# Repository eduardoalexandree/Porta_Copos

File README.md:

# Porta_Copos
TCC Engenharia Eletrônica, Eduardo Alexandre

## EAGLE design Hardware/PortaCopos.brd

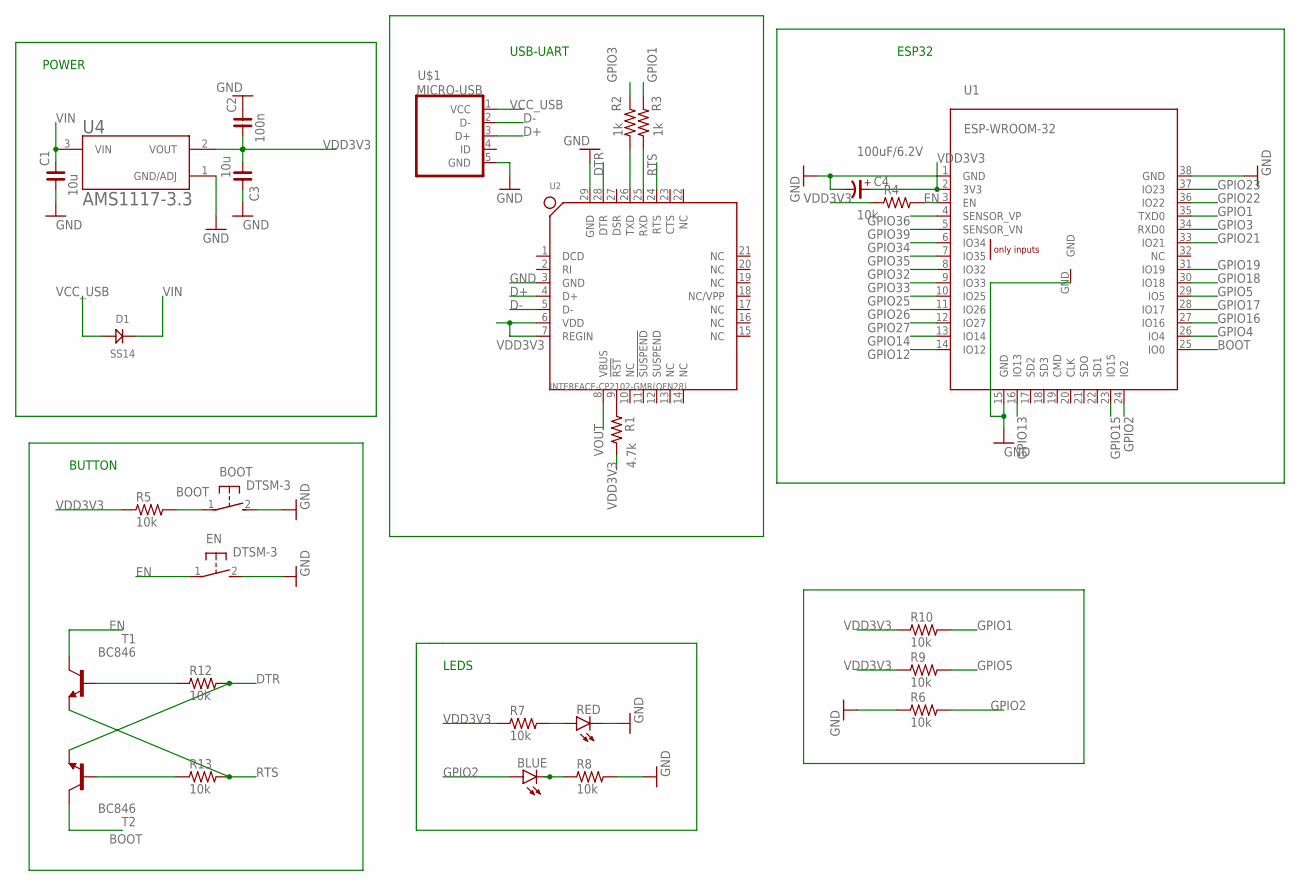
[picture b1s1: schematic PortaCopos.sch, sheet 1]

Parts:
BLUE: blue; CHIPLED_0603
BOOT: DTSM-3
C1, C3: 10u; C0603
C2: 100n; C0603
C4: 100uF/6.2V; C3216-18/T
D1: SS14; DO214
EN: DTSM-3
R1: 4.7k; R0603
R2, R3: 1k; R0603
R4, R5, R6, R7, R8, R9, R10, R12, R13: 10k; R0603
RED: red; CHIPLED_0603
T1, T2: BC846; SOT23
U1: ESP-WROOM-32
U2: INTERFACE-CP2102-GMR(QFN28); QFN28G_0.5-5X5MM
U4: AMS1117-3.3; SOT229P700X180-4N
U$1: MICRO-USB; MICRO-USB-2

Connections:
BOOT: BOOT.1, R5.2, T2.3 (C), U1.25 (IO0)
D+: U2.4 (D+), U$1.3 (D+)
D-: U2.5 (D-), U$1.2 (D-)
DTR: R12.2, T2.2 (E), U2.28 (DTR)
EN: EN.1, R4.2, T1.3 (C), U1.3 (EN)
GND: BOOT.2, C1.1, C2.2, C3.2, C4.-, EN.2, R6.1, R8.2, RED.C, U1.1 (GND), U1.15 (GND), U1.38 (GND), U1.GND, U2.3 (GND), U2.29 (GND), U4.1 (GND/ADJ), U$1.5 (GND); also elsewhere on the board
GPIO1: R3.1, R10.2, U1.35 (TXD0)
GPIO2: BLUE.A, R6.2, U1.24 (IO2)
GPIO3: R2.1, U1.34 (RXD0)
GPIO4: U1.26 (IO4); also elsewhere on the board
GPIO5: R9.2, U1.29 (IO5)
GPIO12: U1.14 (IO12)
GPIO13: U1.16 (IO13)
GPIO14: U1.13 (IO14)
GPIO15: U1.23 (IO15)
GPIO16: U1.27 (IO16); also elsewhere on the board
GPIO17: U1.28 (IO17)
GPIO18: U1.30 (IO18)
GPIO19: U1.31 (IO19)
GPIO21: U1.33 (IO21)
GPIO22: U1.36 (IO22)
GPIO23: U1.37 (IO23)
GPIO25: U1.10 (IO25)
GPIO26: U1.11 (IO26)
GPIO27: U1.12 (IO27)
GPIO32: U1.8 (IO32)
GPIO33: U1.9 (IO33)
GPIO34: U1.6 (IO34)
GPIO35: U1.7 (IO35)
GPIO36: U1.4 (SENSOR_VP)
GPIO39: U1.5 (SENSOR_VN)
unnamed: R1.1, U2.9 (!RST)
unnamed: R2.2, U2.26 (TXD)
unnamed: R3.2, U2.25 (RXD)
unnamed: R12.1, T1.1 (B)
unnamed: R13.1, T2.1 (B)
unnamed: BLUE.C, R8.1
unnamed: R7.2, RED.A
RTS: R13.2, T1.2 (E), U2.24 (RTS)
VCC_USB: D1.ANODE, U$1.1 (VCC)
VDD3V3: C2.1, C3.1, C4.+, R1.2, R4.1, R5.1, R7.1, R9.1, R10.1, U1.2 (3V3), U2.6 (VDD), U2.7 (REGIN), U4.2 (VOUT); also elsewhere on the board
VIN: C1.2, D1.CATHODE (KATHODE), U4.3 (VIN)
VOUT: U2.8 (VBUS)

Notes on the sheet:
POWER
ESP32
USB-UART
BUTTON
LEDS

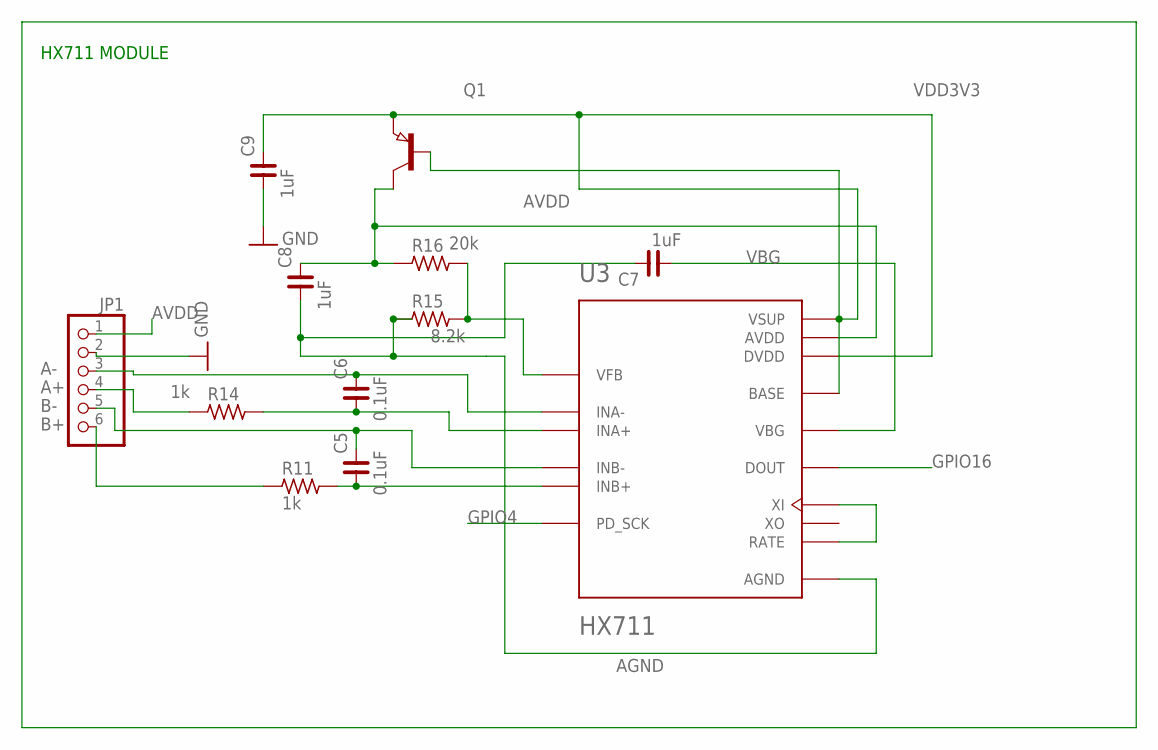
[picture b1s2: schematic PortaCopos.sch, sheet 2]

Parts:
C5, C6: 0.1uF; C0805
C7, C8, C9: 1uF; C0805
JP1: PINHD-1X6; 1X06
Q1: PNP-TRANSISTOR_SOT23; SOT23
R11, R14: 1k; R0603
R15: 8.2k; R0603
R16: 20k; R0603
U3: HX711; SOP127P600X180-16N

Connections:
A+: JP1.4, R14.1
A-: C6.2, JP1.3, U3.7 (INA-)
AGND: C7.2, C8.1, R15.1, U3.5 (AGND)
AVDD: C8.2, JP1.1, Q1.3 (C), R16.1, U3.3 (AVDD)
B+: JP1.6, R11.1
B-: C5.2, JP1.5, U3.9 (INB-)
GND: C9.1, JP1.2; also elsewhere on the board
GPIO4: U3.11 (PD_SCK); also elsewhere on the board
GPIO16: U3.12 (DOUT); also elsewhere on the board
unnamed: U3.14 (XI), U3.15 (RATE)
unnamed: C5.1, R11.2, U3.10 (INB+)
unnamed: C6.1, R14.2, U3.8 (INA+)
unnamed: R15.2, R16.2, U3.4 (VFB)
VBG: C7.1, U3.6 (VBG)
VDD3V3: C9.2, Q1.1 (B), Q1.2 (E), U3.1 (VSUP), U3.2 (BASE), U3.16 (DVDD); also elsewhere on the board

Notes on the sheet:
HX711 MODULE

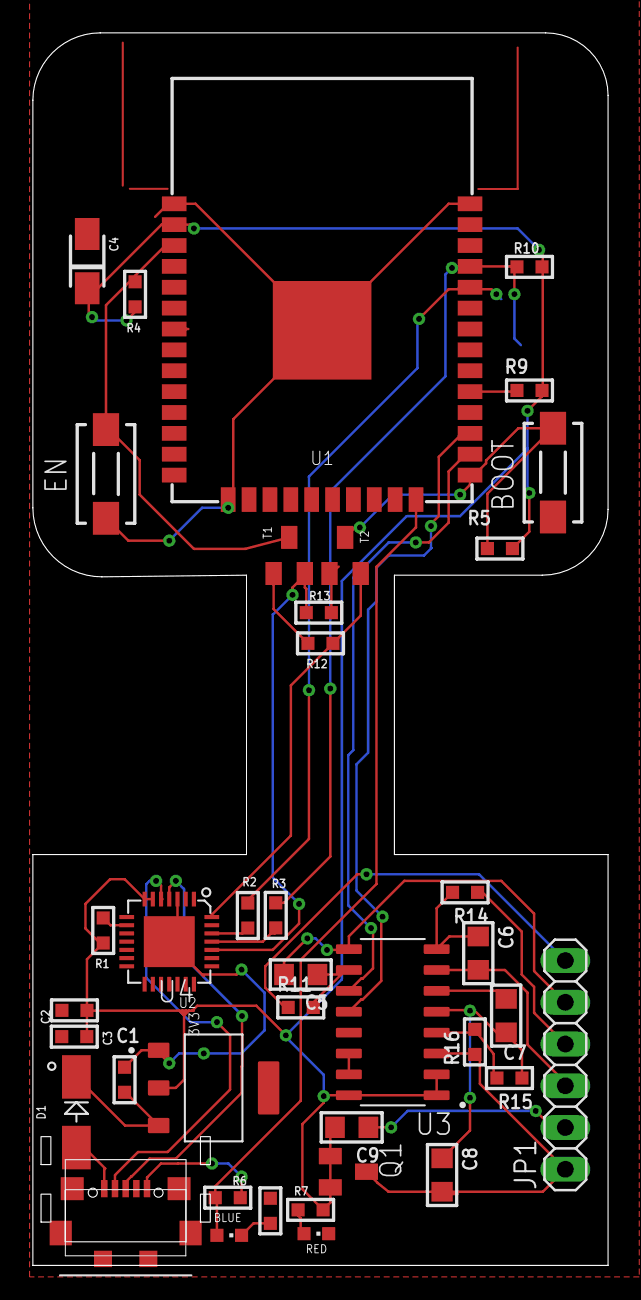
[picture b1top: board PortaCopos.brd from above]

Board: 2 copper layers, 35.0 x 75.0 mm, 39 parts (0 on the bottom side), 34 nets.

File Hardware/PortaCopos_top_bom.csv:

Comment,Designator,Footprint,LCSC Part #
0.1uF,C5 C6,C0805,
1k,R2 R3 R11 R14,R0603,
1uF,C7 C8 C9,C0805,
4.7k,R1,R0603,
8.2k,R15,R0603,
10k,R4 R5 R6 R7 R8 R9 R10 R12 R13,R0603,
10u,C1 C3,C0603,
20k,R16,R0603,
100n,C2,C0603,
100uF/6.2V,C4,C3216-18/T,
AMS1117-3.3,U4,SOT229P700X180-4N,
BC846,T1 T2,SOT23,
DTSM-3,BOOT EN,DTSM-3,
ESP-WROOM-32,U1,ESP-WROOM-32,
HX711,U3,SOP127P600X180-16N,
INTERFACE-CP2102-GMR(QFN28),U2,QFN28G_0.5-5X5MM,
MICRO-USB,U$1,MICRO-USB-2,
SS14,D1,DO214,
blue,BLUE,CHIPLED_0603,
red,RED,CHIPLED_0603,
8550 2ty,Q1 ,,

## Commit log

2023-09-21 first_commit
2023-09-21 adicionar arquivos de esquematico e impressao 3d

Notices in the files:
parts and their libraries:
rc-master-smd: Copyright (C) 2007, Bob Starr
